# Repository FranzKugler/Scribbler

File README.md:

# Scribbler

A wall-hanging two-belt pen plotter: the bot hangs from two belts running to two anchors on the
wall, two steppers wind them, a servo lifts the pen. This repository holds its firmware, its web
interface and its circuit board.

**Status:** the firmware and the web interface are complete up to drawing jobs from the SD card
through a look-ahead planner. None of it has run on hardware yet — the board is being designed.
The open items are in [PLAN.md](PLAN.md).

## What it does

- **Calibration in the browser**, step by step: anchor distance, belts wound in to their stop,
  out to the home position, loops hung on the anchors, pulley and pen calibration.
- **Jobs from a microSD card**, uploaded through the web interface. The format is Mural's, so a
  file made by [Mural's web UI](https://github.com/nikivanov/mural) plots unchanged. Each job is
  checked against the drawing area before the pen moves; progress, pause, resume and cancel.
- **Smooth motion**: a look-ahead planner (junction deviation, trapezoidal ramps) in Cartesian
  millimetres, sliced every 5 ms, each slice solved through Mural's rigid-body kinematic model
  (the bot tilts; belt stretch and the offset to the wall are corrected) and handed to both
  steppers in lockstep.
- **The house scaffolding**: own setup portal, German/English web UI, a password for the
  hardware, update, log and storage tabs; updates over the air from a GitHub release channel
  (stable or edge); a browser flashing page for a blank board.

## Hardware

Own board in [hardware/pcb](hardware/pcb) (KiCad): Seeed XIAO ESP32-S3 Plus, two TMC2240
stepper drivers on SPI, BMI270 IMU for the bot's tilt, SSD1306 OLED, microSD, USB-C PD input.
The pin map is [src/Board.h](src/Board.h). Mechanics — bot, pulleys, anchors — are Mural's.

## Getting it onto a board

- **Blank board:** the flashing page at
  [franzkugler.github.io/Scribbler](https://franzkugler.github.io/Scribbler/) — Chrome or Edge,
  a USB-C cable into the XIAO, one click.
- **From source:** PlatformIO (the pioarduino fork, pinned in `platformio.ini`) and Node.js.

  ```
  npm install && npm run build      # web interface -> data/
  pio run -t upload                 # firmware
  pio run -t uploadfs               # web interface
  pio test -e native                # host tests: kinematics, job format, planner
  npm run dev                       # web interface against a mock of the device, no hardware
  ```

After flashing, the board opens an access point named `Scribbler`; join it and the setup page
asks for the WiFi. Then it answers at `http://scribbler.local`.

## Releases

Every push to `main` builds an **edge** pre-release; a `v*` tag builds a **stable** release and
redeploys the flashing page. Devices follow the channel set in their Update tab.

## Documentation

[PLAN.md](PLAN.md) holds the scope, the hardware decisions and the phases;
[CLAUDE.md](CLAUDE.md) the module layout, the REST API and the conventions. The project language
is English; the web interface speaks German and English, following the browser.

## Credits and licence

The mechanics, the kinematic model and the job format follow
[nikivanov/mural](https://github.com/nikivanov/mural) by Nik Ivanov, licensed under
[CC BY-NC 4.0](https://creativecommons.org/licenses/by-nc/4.0/). Scribbler re-implements them;
it does not vendor Mural's code. Scribbler itself is under the same licence — see [LICENSE](LICENSE).

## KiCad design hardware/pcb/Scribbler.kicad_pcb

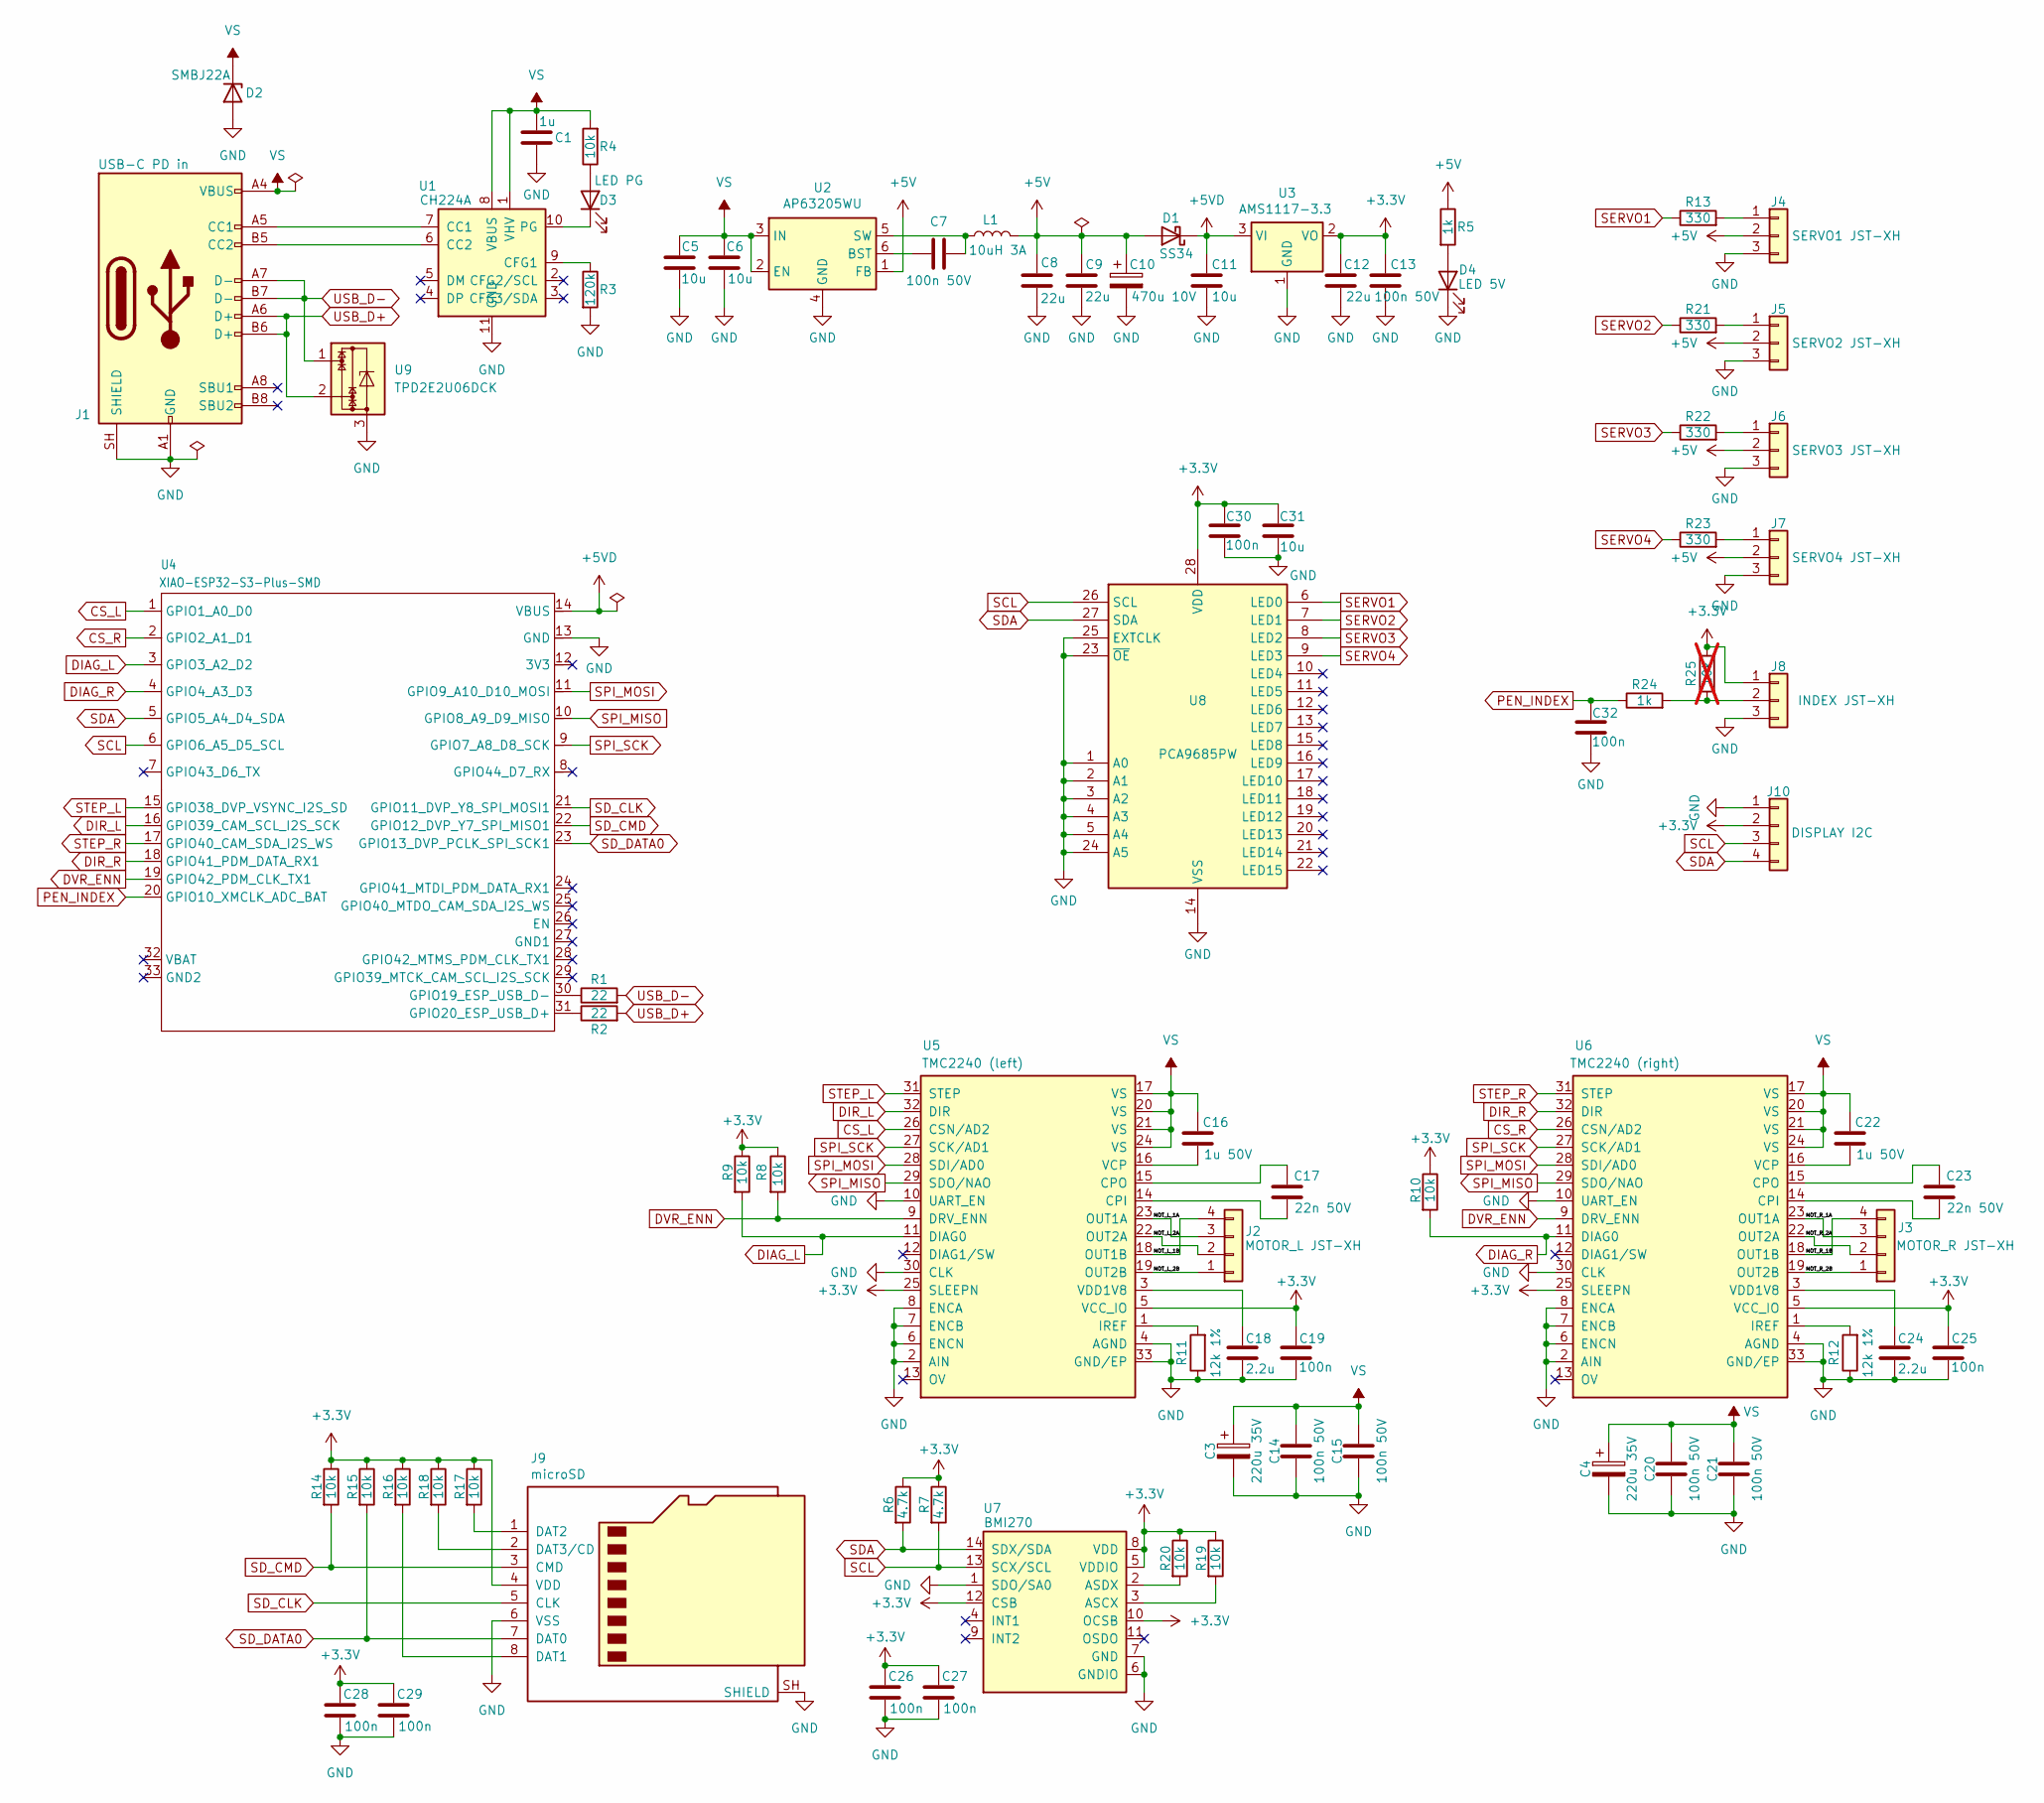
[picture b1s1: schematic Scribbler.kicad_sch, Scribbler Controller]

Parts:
C1: 1u; C_0603_1608Metric; LCSC Part # C1592
C3, C4: 220u 35V; CP_Elec_8x10.5; LCSC Part # C4747976
C5, C6, C11: 10u; C_1206_3216Metric; LCSC Part # C13585
C7, C13, C14, C15, C20, C21: 100n 50V; C_0402_1005Metric; LCSC Part # C1581
C8, C9, C12: 22u; C_0805_2012Metric; LCSC Part # C45783
C10: 470u 10V; CP_Elec_6.3x7.7; LCSC Part # C335982
C16, C22: 1u 50V; C_0603_1608Metric; LCSC Part # C15849
C17, C23: 22n 50V; C_0402_1005Metric; LCSC Part # C1532
C18, C24: 2.2u; C_0805_2012Metric; LCSC Part # C19110
C19, C25, C26, C27, C28, C29, C30, C32: 100n; C_0402_1005Metric; LCSC Part # C1581
C31: 10u; C_0805_2012Metric; LCSC Part # C13585
D1: SS34; D_SMA; LCSC Part # C8678
D2: SMBJ22A; D_SMB; LCSC Part # C151920
D3: LED PG; LED_0603_1608Metric; LCSC Part # C2286
D4: LED 5V; LED_0603_1608Metric; LCSC Part # C2286
J1: USB-C PD in; USB_C_Receptacle_HRO_TYPE-C-31-M-12; LCSC Part # C165948
J2: MOTOR_L JST-XH; 2_54-4P-LT; LCSC Part # C722700
J3: MOTOR_R JST-XH; 2_54-4P-LT; LCSC Part # C722700
J4: SERVO1 JST-XH; 2_54-3P-LT; LCSC Part # C722698
J5: SERVO2 JST-XH; 2_54-3P-LT; LCSC Part # C722698
J6: SERVO3 JST-XH; 2_54-3P-LT; LCSC Part # C722698
J7: SERVO4 JST-XH; 2_54-3P-LT; LCSC Part # C722698
J8: INDEX JST-XH; 2_54-3P-LT; LCSC Part # C722698
J9: microSD; microSD_HC_Hirose_DM3AT-SF-PEJM5; LCSC Part # C114218
J10: DISPLAY I2C; 2_54-4P-LT; LCSC Part # C722700
L1: 10uH 3A; L_Changjiang_FXL0518; LCSC Part # C475910
R1, R2: 22; R_0402_1005Metric; LCSC Part # C25092
R3: 120k; R_0402_1005Metric; LCSC Part # C25796
R4, R8, R9, R10, R14, R15, R16, R17, R18, R19, R20: 10k; R_0402_1005Metric; LCSC Part # C25744
R5, R24: 1k; R_0402_1005Metric; LCSC Part # C11702
R6, R7: 4.7k; R_0402_1005Metric; LCSC Part # C25900
R11, R12: 12k 1%; R_0402_1005Metric; LCSC Part # C25752
R13, R21, R22, R23: 330; R_0402_1005Metric; LCSC Part # C25104
R25: 10k; R_0402_1005Metric; LCSC Part # C25744; not fitted
U1: CH224A; SSOP-10-1EP_3.9x4.9mm_P1mm_EP2.1x3.3mm; LCSC Part # C42459160
U2: AP63205WU; TSOT-23-6; LCSC Part # C2071056
U3: AMS1117-3.3; SOT-223-3_TabPin2; LCSC Part # C6186
U4: XIAO-ESP32-S3-Plus-SMD
U5: TMC2240 (left); TQFN-32-1EP_5x5mm_P0.5mm_EP3.4x3.4mm; LCSC Part # C7429724
U6: TMC2240 (right); TQFN-32-1EP_5x5mm_P0.5mm_EP3.4x3.4mm; LCSC Part # C7429724
U7: BMI270; Bosch_LGA-14_3x2.5mm_P0.5mm; LCSC Part # C2836813
U8: PCA9685PW; TSSOP-28_4.4x9.7mm_P0.65mm; LCSC Part # C2678753
U9: TPD2E2U06DCK; SOT-323_SC-70; LCSC Part # C5350871

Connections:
+3.3V: C12.1, C13.1, C19.2, C25.2, C26.1, C27.1, C28.1, C29.1, C30.1, C31.1, J8.1, J9.4 (VDD), J10.2, R6.1, R7.1, R8.1, R9.1, R10.1, R14.1, R15.1, R16.1, R17.1, R18.1, R19.1, R20.1, R25.2, U3.2 (VO), U5.5 (VCC_IO), U5.25 (SLEEPN), U6.5 (VCC_IO), U6.25 (SLEEPN), U7.5 (VDDIO), U7.8 (VDD), U7.10 (OCSB), U7.12 (CSB), U8.28 (VDD)
+5V: C8.1, C9.1, C10.1, D1.2 (A), J4.2, J5.2, J6.2, J7.2, L1.2, R5.1, U2.1 (FB)
+5VD: C11.1, D1.1 (K), U3.3 (VI), U4.14 (VBUS)
/MOT_L_1A: J2.3, U5.23 (OUT1A)
/MOT_L_1B: J2.4, U5.18 (OUT1B)
/MOT_L_2A: J2.2, U5.22 (OUT2A)
/MOT_L_2B: J2.1, U5.19 (OUT2B)
/MOT_R_1A: J3.3, U6.23 (OUT1A)
/MOT_R_1B: J3.4, U6.18 (OUT1B)
/MOT_R_2A: J3.2, U6.22 (OUT2A)
/MOT_R_2B: J3.1, U6.19 (OUT2B)
CS_L: U4.1 (GPIO1_A0_D0), U5.26 (CSN/AD2)
CS_R: U4.2 (GPIO2_A1_D1), U6.26 (CSN/AD2)
DIAG_L: R9.2, U4.3 (GPIO3_A2_D2), U5.11 (DIAG0)
DIAG_R: R10.2, U4.4 (GPIO4_A3_D3), U6.11 (DIAG0)
DIR_L: U4.16 (GPIO39_CAM_SCL_I2S_SCK), U5.32 (DIR)
DIR_R: U4.18 (GPIO41_PDM_DATA_RX1), U6.32 (DIR)
DVR_ENN: R8.2, U4.19 (GPIO42_PDM_CLK_TX1), U5.9 (DRV_ENN), U6.9 (DRV_ENN)
GND: C1.2, C3.2, C4.2, C5.2, C6.2, C8.2, C9.2, C10.2, C11.2, C12.2, C13.2, C14.2, C15.2, C18.1, C19.1, C20.2, C21.2, C24.1, C25.1, C26.2, C27.2, C28.2, C29.2, C30.2, C31.2, C32.2, D2.2 (A), D4.1 (K), J1.A1 (GND), J1.A12 (GND), J1.B1 (GND), J1.B12 (GND), J1.SH (SHIELD), J4.3, J5.3, J6.3, J7.3, J8.3, J9.6 (VSS), J9.SH (SHIELD), J10.1, R3.2, R11.1, R12.1, U1.11 (GND), U2.4 (GND), U3.1 (GND), U4.13 (GND), U5.2 (AIN), U5.4 (AGND), U5.6 (ENCN), U5.7 (ENCB), U5.8 (ENCA), U5.10 (UART_EN), U5.30 (CLK), U5.33 (GND/EP), U6.2 (AIN), U6.4 (AGND), U6.6 (ENCN), U6.7 (ENCB), U6.8 (ENCA), U6.10 (UART_EN), U6.30 (CLK), U6.33 (GND/EP), U7.1 (SDO/SA0), U7.6 (GNDIO), U7.7 (GND), U8.1 (A0), U8.2 (A1), U8.3 (A2), U8.4 (A3), U8.5 (A4), U8.14 (VSS), U8.23 (~OE), U8.24 (A5), U8.25 (EXTCLK), U9.3; also elsewhere on the board
unnamed: D3.2 (A), R4.1
unnamed: D3.1 (K), U1.10 (PG)
unnamed: D4.2 (A), R5.2
unnamed: J1.A5 (CC1), U1.7 (CC1)
unnamed: J1.B5 (CC2), U1.6 (CC2)
unnamed: J4.1, R13.2
unnamed: J5.1, R21.2
unnamed: J6.1, R22.2
unnamed: J7.1, R23.2
unnamed: J8.2, R24.2, R25.1
unnamed: J9.8 (DAT1), R16.2
unnamed: J9.1 (DAT2), R17.2
unnamed: J9.2 (DAT3/CD), R18.2
unnamed: R3.1, U1.9 (CFG1)
unnamed: C7.1, U2.6 (BST)
unnamed: C7.2, L1.1, U2.5 (SW)
unnamed: R1.1, U4.30 (GPIO19_ESP_USB_D-)
unnamed: R2.1, U4.31 (GPIO20_ESP_USB_D+)
unnamed: C17.1, U5.14 (CPI)
unnamed: C17.2, U5.15 (CPO)
unnamed: R11.2, U5.1 (IREF)
unnamed: C16.1, U5.16 (VCP)
unnamed: C18.2, U5.3 (VDD1V8)
unnamed: C23.1, U6.14 (CPI)
unnamed: C23.2, U6.15 (CPO)
unnamed: R12.2, U6.1 (IREF)
unnamed: C22.1, U6.16 (VCP)
unnamed: C24.2, U6.3 (VDD1V8)
unnamed: R19.2, U7.3 (ASCX)
unnamed: R20.2, U7.2 (ASDX)
PEN_INDEX: C32.1, R24.1, U4.20 (GPIO10_XMCLK_ADC_BAT)
SCL: J10.3, R7.2, U4.6 (GPIO6_A5_D5_SCL), U7.13 (SCX/SCL), U8.26 (SCL)
SDA: J10.4, R6.2, U4.5 (GPIO5_A4_D4_SDA), U7.14 (SDX/SDA), U8.27 (SDA)
SD_CLK: J9.5 (CLK), U4.21 (GPIO11_DVP_Y8_SPI_MOSI1)
SD_CMD: J9.3 (CMD), R14.2, U4.22 (GPIO12_DVP_Y7_SPI_MISO1)
SD_DATA0: J9.7 (DAT0), R15.2, U4.23 (GPIO13_DVP_PCLK_SPI_SCK1)
SERVO1: R13.1, U8.6 (LED0)
SERVO2: R21.1, U8.7 (LED1)
SERVO3: R22.1, U8.8 (LED2)
SERVO4: R23.1, U8.9 (LED3)
SPI_MISO: U4.10 (GPIO8_A9_D9_MISO), U5.29 (SDO/NAO), U6.29 (SDO/NAO)
SPI_MOSI: U4.11 (GPIO9_A10_D10_MOSI), U5.28 (SDI/AD0), U6.28 (SDI/AD0)
SPI_SCK: U4.9 (GPIO7_A8_D8_SCK), U5.27 (SCK/AD1), U6.27 (SCK/AD1)
STEP_L: U4.15 (GPIO38_DVP_VSYNC_I2S_SD), U5.31 (STEP)
STEP_R: U4.17 (GPIO40_CAM_SDA_I2S_WS), U6.31 (STEP)
USB_D+: J1.A6 (D+), J1.B6 (D+), R2.2, U9.2
USB_D-: J1.A7 (D-), J1.B7 (D-), R1.2, U9.1
VS: C1.1, C3.1, C4.1, C5.1, C6.1, C14.1, C15.1, C16.2, C20.1, C21.1, C22.2, D2.1 (K), J1.A4 (VBUS), J1.A9 (VBUS), J1.B4 (VBUS), J1.B9 (VBUS), R4.2, U1.1 (VHV), U1.8 (VBUS), U2.2 (EN), U2.3 (IN), U5.17 (VS), U5.20 (VS), U5.21 (VS), U5.24 (VS), U6.17 (VS), U6.20 (VS), U6.21 (VS), U6.24 (VS)

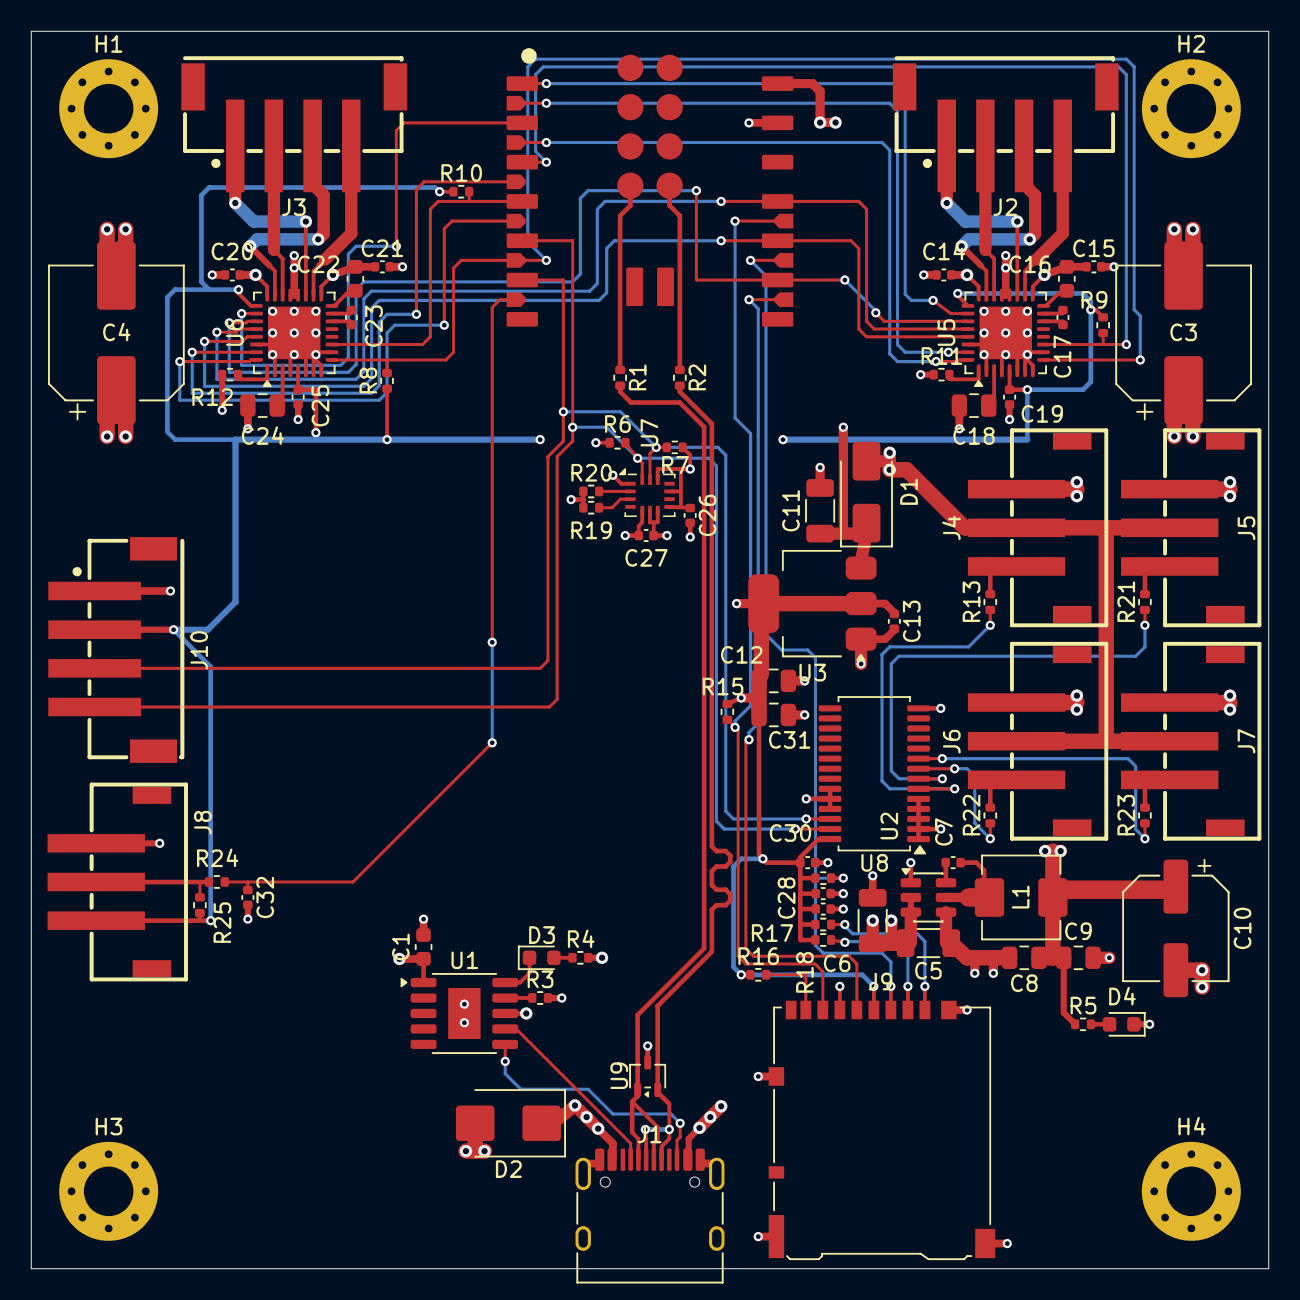
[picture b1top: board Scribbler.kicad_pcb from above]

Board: 4 copper layers, 80.0 x 80.0 mm, 84 parts (0 on the bottom side), 67 nets.

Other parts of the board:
H1, H2, H3, H4: MountingHole_3.2mm_M3_Pad_Via

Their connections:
GND: H1.1, H2.1, H3.1, H4.1; also elsewhere on the board

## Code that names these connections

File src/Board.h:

/**
 * Board
 * The pin map and the fixed facts of the board - the only file that knows
 * which GPIO does what.
 *
 * Taken from the netlist of hardware/pcb/Scribbler_pretty.kicad_sch (the
 * finished schematic, 15.11.2026; the GPIO map is identical to the earlier
 * Scribbler.kicad_sch), not from the XIAO wiki: Seeed's pages disagree about
 * the Plus's back pads D11-D19, and the schematic symbol is what the board
 * will actually be routed from. If the schematic changes, regenerate the netlist and compare
 * - nothing checks this file against it automatically.
 *
 * It is not configurable at runtime. A setting for a pin number is a way to
 * drive a motor coil from the SD card's clock line by mistake.
 *
 * The breadboard rig (PLAN.md section 0) is wired to these same pins, so the
 * firmware does not need a second map. TMC2240 breakout boards in SPI mode
 * stand in for the on-board drivers.
 *
 * @mc       ESP32S3
 * @author   Franz Kugler / franz _AT_ franz _MINUS_ kugler _DOT_ de
 * @version  1.0
 * @created  15.11.2026
 * @updated  15.11.2026
 */
#ifndef BOARD_H
#define BOARD_H

#include <stdint.h>

namespace Board
{
    // ------ stepper drivers: 2 x TMC2240, SPI mode ------
    //
    // UART_EN is tied to GND on both, which selects SPI; the AD0..AD2 pins
    // double as SDI/SCK/CSN and carry no address. CLK is grounded, so the
    // drivers run on their internal ~12.5 MHz clock.

    constexpr uint8_t SPI_SCK  = 7;   // D8
    constexpr uint8_t SPI_MISO = 8;   // D9
    constexpr uint8_t SPI_MOSI = 9;   // D10

    constexpr uint8_t CS_LEFT  = 1;   // D0
    constexpr uint8_t CS_RIGHT = 2;   // D1

    constexpr uint8_t STEP_LEFT  = 38;  // D11
    constexpr uint8_t DIR_LEFT   = 39;  // D12
    constexpr uint8_t STEP_RIGHT = 40;  // D13
    constexpr uint8_t DIR_RIGHT  = 41;  // D14

    // Shared by both drivers, active low, with a 10k pull-up on the board: the
    // motors stay off while the ESP32 boots and this pin still floats. Drive it
    // low only once the drivers have been configured. (The net is spelled
    // DVR_ENN in the schematic.)
    constexpr uint8_t DRV_ENN = 42;    // D15

    // DIAG0 of each driver. GPIO3 is a strapping pin (JTAG source select),
    // which only matters if the eFuse asks for it - harmless as an input, and
    // the rule in the board's design rules covers STEP/DIR/ENN, not this.
    constexpr uint8_t DIAG_LEFT  = 3;  // D2
    constexpr uint8_t DIAG_RIGHT = 4;  // D3

    // IREF to GND through 12k 1 % on both drivers. The full-scale current is
    // K_IFS / R_REF, with K_IFS set by DRV_CONF.CURRENT_RANGE - see Driver.cpp.
    constexpr float DRIVER_RREF_KOHM = 12.0f;

    // No shaft encoders: the finished schematic dropped the optional J7/J8 and
    // ties each driver's ENCA/ENCB/ENCN to GND. PLAN.md section 0.3 says why
    // they were never more than an option.

    // ------ pen ------

    // Servo signal through 330 R to J4; the servo runs on the board's 5 V.
    constexpr uint8_t SERVO_PWM = 10;  // D16

    // ------ I2C: SSD1306 display (J5) and BMI270 IMU ------

    constexpr uint8_t I2C_SDA = 5;     // D4
    constexpr uint8_t I2C_SCL = 6;     // D5

    constexpr uint8_t DISPLAY_ADDR = 0x3C;
    constexpr uint8_t IMU_ADDR = 0x68;  // SDO/SA0 tied to GND

    // ------ microSD, SD_MMC 1-bit ------
    //
    // On its own pins, never on the drivers' SPI bus: the card wants a slow
    // clock during init, some cards do not release MISO cleanly, and the job
    // runner reads continuously while the motion side talks to the drivers.
    // CMD and DAT0..DAT3 have 10k pull-ups on the board; DAT1..DAT3 are unused.

    constexpr uint8_t SD_CLK  = 13;    // D17
    constexpr uint8_t SD_CMD  = 12;    // D18
    constexpr uint8_t SD_DAT0 = 11;    // D19 (net SD_DATA0)

    // GPIO43/44 (D6/D7, the UART0 pins) are deliberately left free: a serial
    // console that does not depend on USB is worth two pins on a device that
    // hangs on a wall.
}

#endif
